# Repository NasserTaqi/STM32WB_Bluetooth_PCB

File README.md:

# STM32WB Bluetooth PCB
This project is a PCB built around an STM32WB for RF Bluetooth connection.

## Components
- STM32WB
- Crystal Oscillators:
    - HSE 32MHz 
    - LSE 32.768KHz
- 3.3V LDO
- USB C 2.0 + ESD protection
- Bluetooth RF connection via UFL connector + Filtering
- SWD Tag connect
- UART Connection

## Board Setup
The board is 4 layers with the following stack-up:

Layer: 1	SIGNAL

Layer: 2	GND

Layer: 3	GND

Layer: 4	SIGNAL

### Schematic:

### PCB Layout:

### PCB 3D:

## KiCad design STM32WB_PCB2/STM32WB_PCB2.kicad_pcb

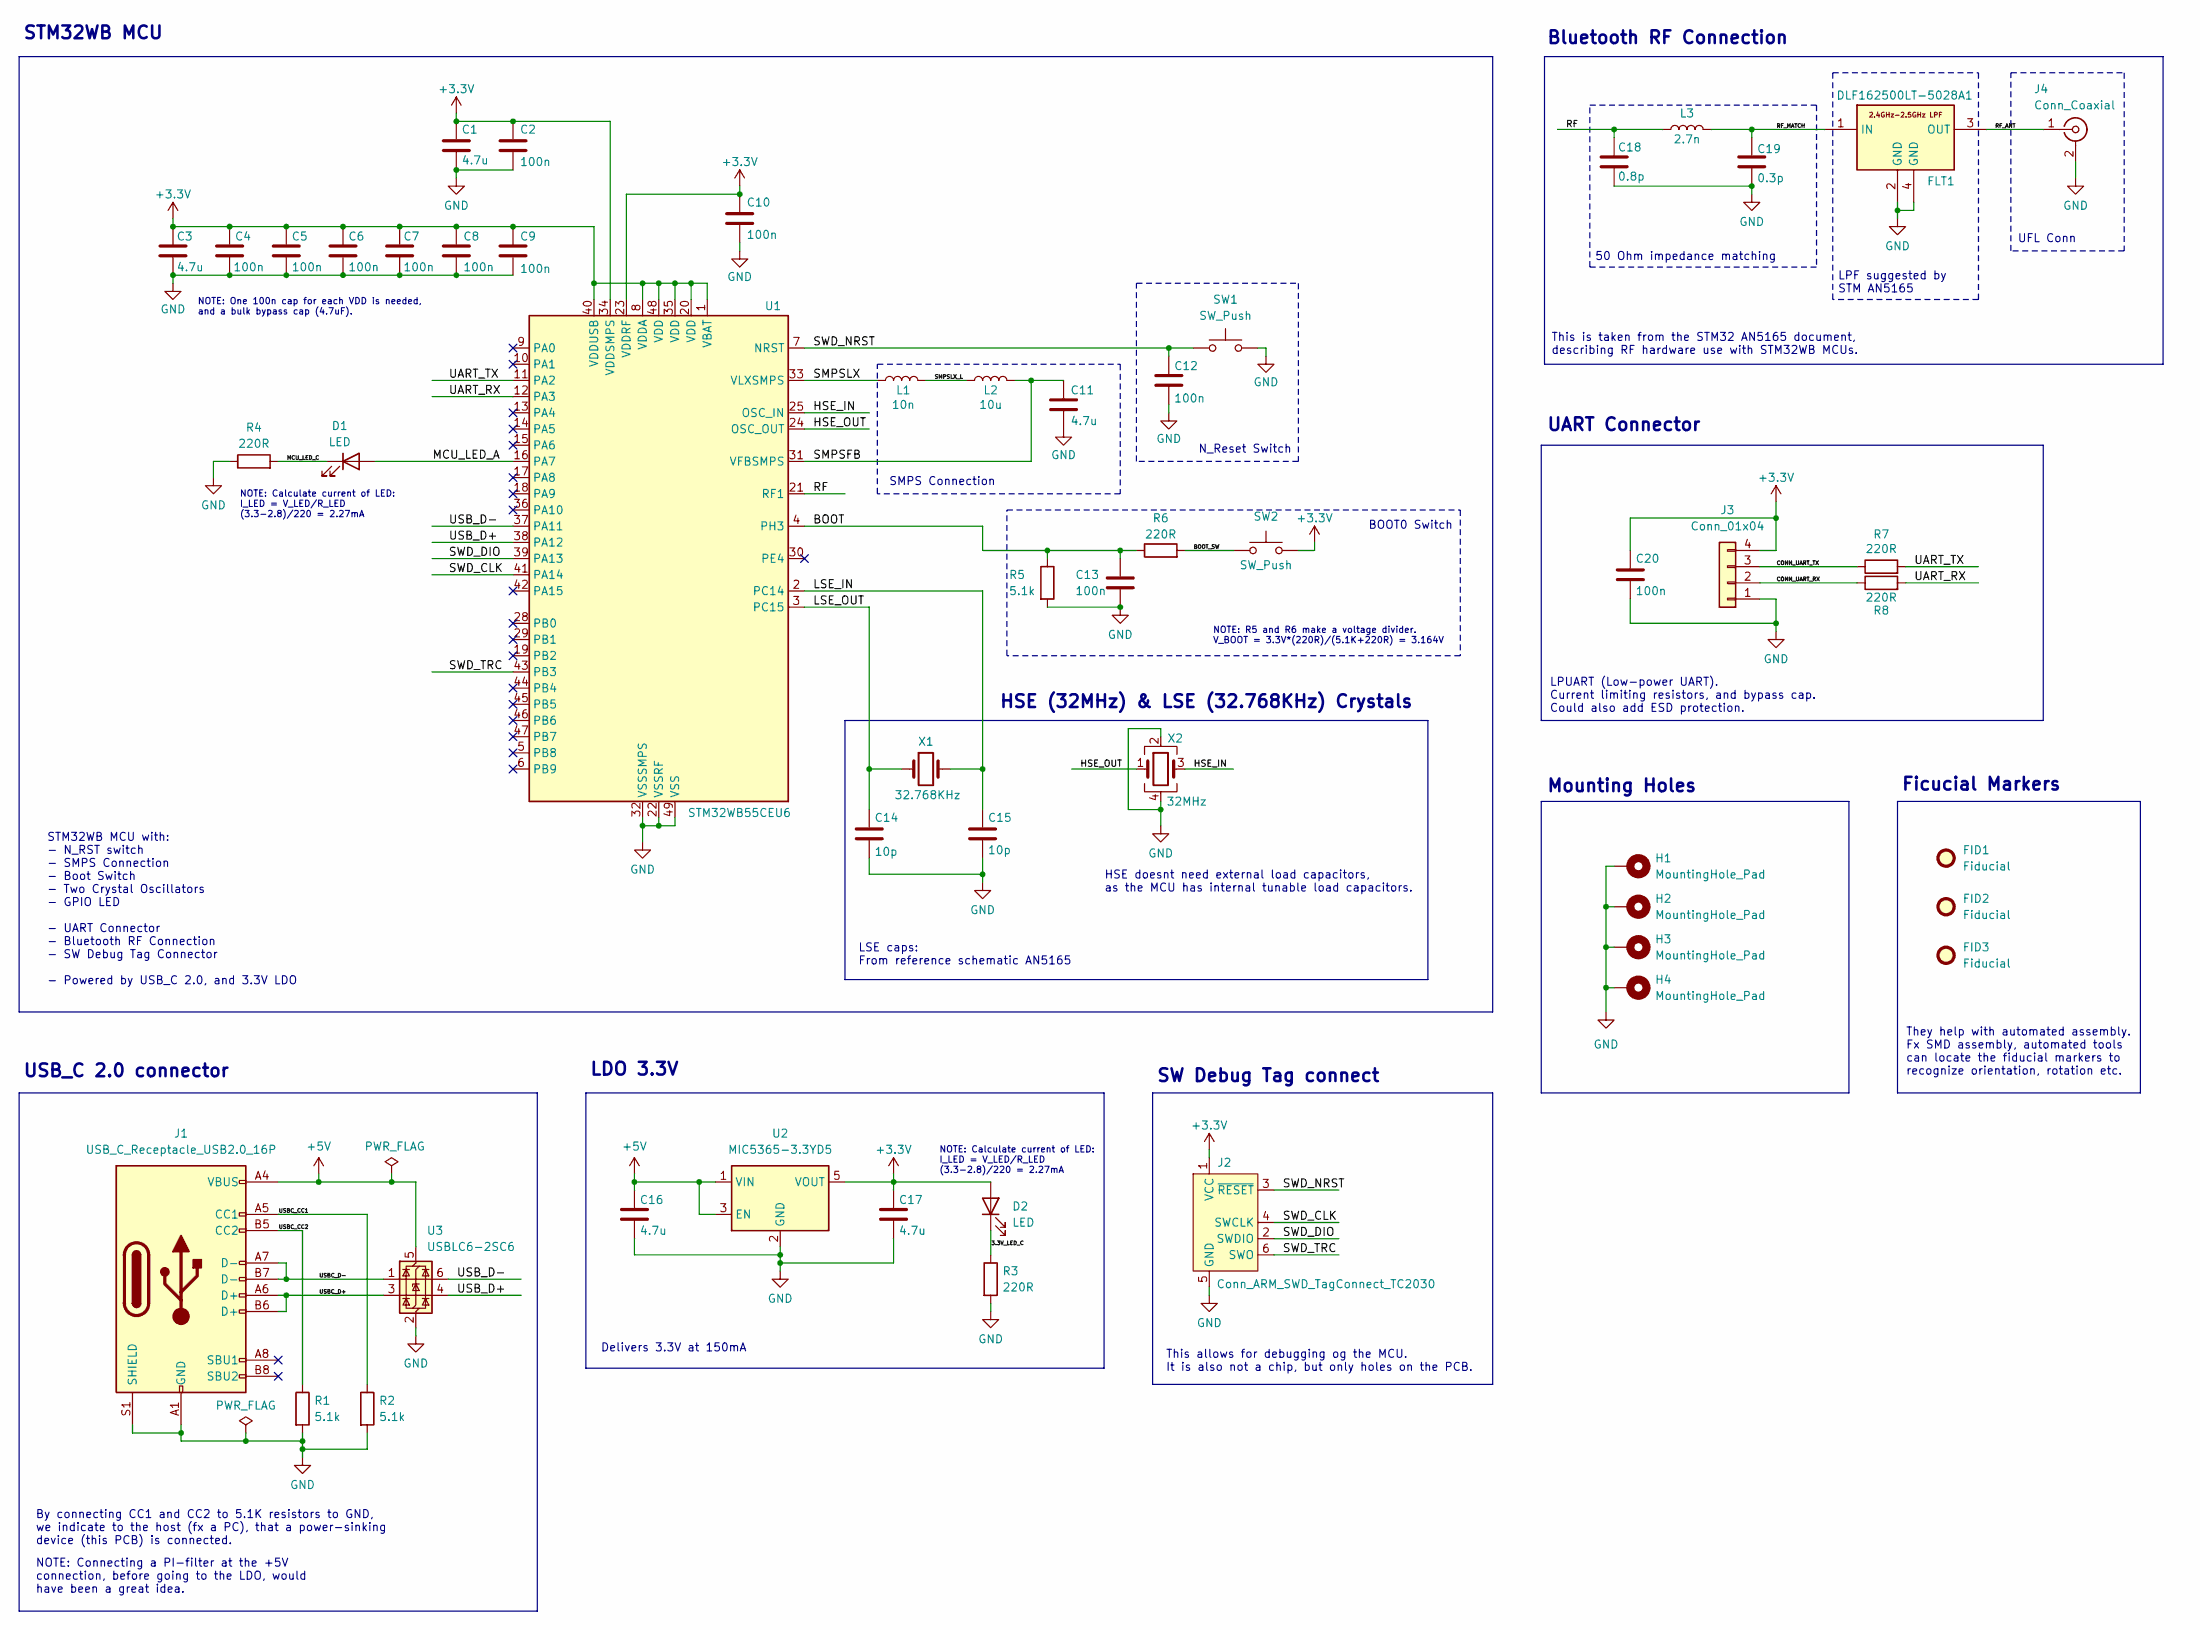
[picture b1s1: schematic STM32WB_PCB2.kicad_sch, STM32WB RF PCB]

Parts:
C1, C3, C11, C16, C17: 4.7u; C_0603_1608Metric; Manufacturer Part Number 0402ZD475KAT2A
C2, C4, C5, C6, C7, C8, C9, C10, C12, C13, C20: 100n; C_0402_1005Metric; Manufacturer Part Number C0402C104K4RAC3121
C14, C15: 10p; C_0402_1005Metric; Manufacturer Part Number C0402C100F8HACTU
C18: 0.8p; C_0402_1005Metric; Manufacturer Part Number GRM1555C1HR80BA01D
C19: 0.3p; C_0402_1005Metric; Manufacturer Part Number GRM1555C1HR30WA01D
D1, D2: LED; LED_0402_1005Metric; Manufacturer Part Number 599-1A90-147F
FID1, FID2, FID3: Fiducial; Fiducial_1mm_Mask2mm
FLT1: DLF162500LT-5028A1; DLF162500LT5028A1; Mouser Part Number 810-DLF16250LT5028A1
H1, H2, H3, H4: MountingHole_Pad; MountingHole_2.2mm_M2_Pad_Via
J1: USB_C_Receptacle_USB2.0_16P; USB_C_Receptacle_GCT_USB4105-xx-A_16P_TopMnt_Horizontal; Manufacturer Part Number USB4105-GF-A
J2: Conn_ARM_SWD_TagConnect_TC2030; Tag-Connect_TC2030-IDC-FP_2x03_P1.27mm_Vertical
J3: Conn_01x04; PinHeader_1x04_P2.54mm_Vertical; Manufacturer Part Number 22-28-4044
J4: Conn_Coaxial; U.FL_Hirose_U.FL-R-SMT-1_Vertical; Manufacturer Part Number U.FL-R-SMT(01)
L1: 10n; L_0402_1005Metric; Manufacturer Part Number LQG15WH10NH02D
L2: 10u; L_0805_2012Metric; Manufacturer Part Number LQM21DH100M70L
L3: 2.7n; L_0402_1005Metric; Manufacturer Part Number LQG15HN2N7C02D
R1, R2, R5: 5.1k; R_0402_1005Metric; Manufacturer Part Number RP0402BRD075K1L
R3, R4, R6, R7, R8: 220R; R_0402_1005Metric; Manufacturer Part Number RT0402BRD07220RL
SW1, SW2: SW_Push; SW_Push_SPST_NO_Alps_SKRK; Manufacturer Part Number SKRKAHE020
U1: STM32WB55CEU6; QFN-48-1EP_7x7mm_P0.5mm_EP5.6x5.6mm; Manufacturer Part Number STM32WB55CEU6
U2: MIC5365-3.3YD5; TSOT-23-5; Manufacturer Part Number MIC5365-3.3YD5-TR
U3: USBLC6-2SC6; SOT-23-6; Manufacturer Part Number USBLC6-2SC6
X1: 32.768KHz; Crystal_SMD_2012-2Pin_2.0x1.2mm; Manufacturer Part Number NX2012SA-32.768K-STD-MUB-1
X2: 32MHz; Crystal_SMD_2016-4Pin_2.0x1.6mm; Manufacturer Part Number NX2016SA-32M-EXS00A-CS06465

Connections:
+3.3V: C1.1, C2.1, C3.1, C4.1, C5.1, C6.1, C7.1, C8.1, C9.1, C10.1, C17.1, C20.1, D2.2 (A), J2.1 (VCC), J3.4, SW2.2, U1.1 (VBAT), U1.8 (VDDA), U1.20 (VDD), U1.23 (VDDRF), U1.34 (VDDSMPS), U1.35 (VDD), U1.40 (VDDUSB), U1.48 (VDD), U2.5 (VOUT)
+5V: C16.1, J1.A4 (VBUS), J1.A9 (VBUS), J1.B4 (VBUS), J1.B9 (VBUS), U2.1 (VIN), U2.3 (EN), U3.5 (VBUS)
/3.3V_LED_C: D2.1 (K), R3.1
/BOOT: C13.1, R5.1, R6.1, U1.4 (PH3)
/BOOT_SW: R6.2, SW2.1
/CONN_UART_RX: J3.2, R8.1
/CONN_UART_TX: J3.3, R7.1
/HSE_IN: U1.25 (OSC_IN), X2.3
/HSE_OUT: U1.24 (OSC_OUT), X2.1
/LSE_IN: C15.1, U1.2 (PC14), X1.2
/LSE_OUT: C14.1, U1.3 (PC15), X1.1
/MCU_LED_A: D1.2 (A), U1.16 (PA7)
/MCU_LED_C: D1.1 (K), R4.2
/RF: C18.1, L3.1, U1.21 (RF1)
/RF_ANT: FLT1.3 (OUT), J4.1 (In)
/RF_MATCH: C19.1, FLT1.1 (IN), L3.2
/SMPSFB: C11.1, L2.2, U1.31 (VFBSMPS)
/SMPSLX: L1.1, U1.33 (VLXSMPS)
/SMPSLX_L: L1.2, L2.1
/SWD_CLK: J2.4 (SWCLK), U1.41 (PA14)
/SWD_DIO: J2.2 (SWDIO), U1.39 (PA13)
/SWD_NRST: C12.1, J2.3 (~RESET), SW1.1, U1.7 (NRST)
/SWD_TRC: J2.6 (SWO), U1.43 (PB3)
/UART_RX: R8.2, U1.12 (PA3)
/UART_TX: R7.2, U1.11 (PA2)
/USBC_CC1: J1.A5 (CC1), R2.1
/USBC_CC2: J1.B5 (CC2), R1.1
/USBC_D+: J1.A6 (D+), J1.B6 (D+), U3.3 (I/O2)
/USBC_D-: J1.A7 (D-), J1.B7 (D-), U3.1 (I/O1)
/USB_D+: U1.38 (PA12), U3.4 (I/O2)
/USB_D-: U1.37 (PA11), U3.6 (I/O1)
GND: C1.2, C2.2, C3.2, C4.2, C5.2, C6.2, C7.2, C8.2, C9.2, C10.2, C11.2, C12.2, C13.2, C14.2, C15.2, C16.2, C17.2, C18.2, C19.2, C20.2, FLT1.2 (GND), FLT1.4 (GND), H1.1, H2.1, H3.1, H4.1, J1.A1 (GND), J1.A12 (GND), J1.B1 (GND), J1.B12 (GND), J1.S1 (SHIELD), J2.5 (GND), J3.1, J4.2 (Ext), R1.2, R2.2, R3.2, R4.1, R5.2, SW1.2, U1.22 (VSSRF), U1.32 (VSSSMPS), U1.49 (VSS), U2.2 (GND), U3.2 (GND), X2.2, X2.4

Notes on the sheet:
UFL Conn
STM32WB MCU with: - N_RST switch - SMPS Connection - Boot Switch - Two Crystal Oscillators - GPIO LED - UART Connector - Bluetooth RF Connection - SW Debug Tag Connector - Powered by USB_C 2.0, and 3.3V LDO
NOTE: R5 and R6 make a voltage divider. V_BOOT = 3.3V*(220R)/(5.1K+220R) = 3.164V
Mounting Holes
NOTE: One 100n cap for each VDD is needed, and a bulk bypass cap (4.7uF).
BOOT0 Switch
UART Connector
Ficucial Markers
HSE (32MHz) & LSE (32.768KHz) Crystals
LSE caps: From reference schematic AN5165
SW Debug Tag connect
LDO 3.3V
By connecting CC1 and CC2 to 5.1K resistors to GND, we indicate to the host (fx a PC), that a power-sinking device (this PCB) is connected.
They help with automated assembly. Fx SMD assembly, automated tools can locate the fiducial markers to recognize orientation, rotation etc.
LPUART (Low-power UART). Current limiting resistors, and bypass cap. Could also add ESD protection.
Delivers 3.3V at 150mA
This allows for debugging og the MCU. It is also not a chip, but only holes on the PCB.
SMPS Connection
This is taken from the STM32 AN5165 document, describing RF hardware use with STM32WB MCUs.
NOTE: Calculate current of LED: I_LED = V_LED/R_LED (3.3-2.8)/220 = 2.27mA
N_Reset Switch
Bluetooth RF Connection
50 Ohm impedance matching
HSE doesnt need external load capacitors, as the MCU has internal tunable load capacitors.
STM32WB MCU
USB_C 2.0 connector
NOTE: Connecting a PI-filter at the +5V connection, before going to the LDO, would have been a great idea.
LPF suggested by STM AN5165

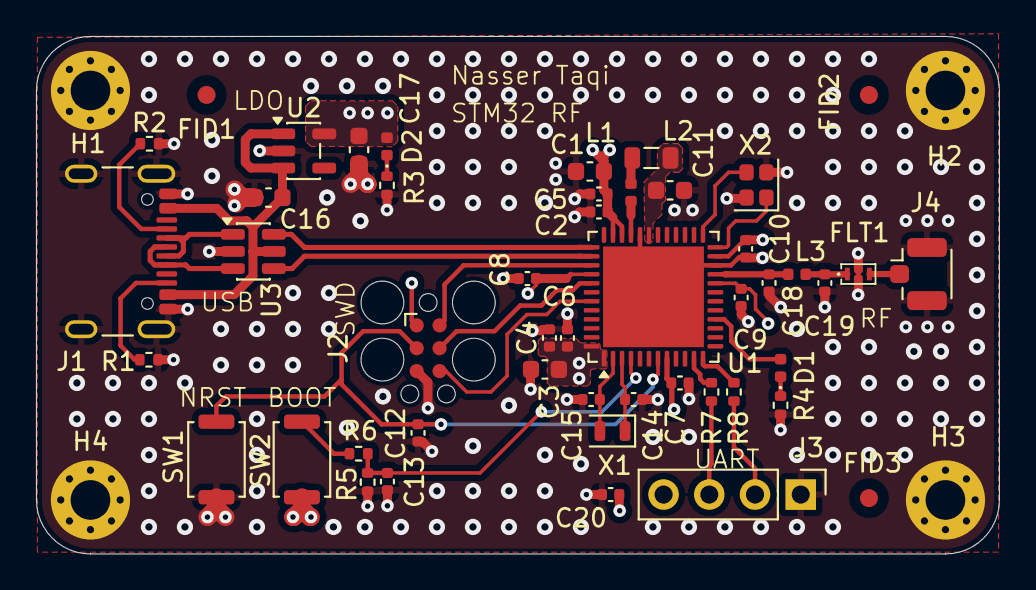
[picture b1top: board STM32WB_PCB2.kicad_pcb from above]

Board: 4 copper layers, 53.5 x 28.8 mm, 52 parts (0 on the bottom side), 32 nets.

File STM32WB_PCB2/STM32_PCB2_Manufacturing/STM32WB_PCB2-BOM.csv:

"Reference","Value","Footprint","Description","Manufacturer","Manufacturer Part Number","Distributor Link","Qty"
"C1,C3,C11,C16,C17","4.7u","Capacitor_SMD:C_0603_1608Metric","Unpolarized capacitor","KYOCERA AVX","0402ZD475KAT2A","https://www.mouser.dk/ProductDetail/KYOCERA-AVX/0402ZD475KAT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","5"
"C2,C4,C5,C6,C7,C8,C9,C10,C12,C13,C20","100n","Capacitor_SMD:C_0402_1005Metric","Unpolarized capacitor","KEMET","C0402C104K4RAC3121","https://www.mouser.dk/ProductDetail/KEMET/C0402C104K4RAC3121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","11"
"C14,C15","10p","Capacitor_SMD:C_0402_1005Metric","Unpolarized capacitor","KEMET","C0402C100F8HACTU","https://www.mouser.dk/ProductDetail/KEMET/C0402C100F8HACTU?q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","2"
"C18","0.8p","Capacitor_SMD:C_0402_1005Metric","Unpolarized capacitor","Murata Electronics","GRM1555C1HR80BA01D","https://www.mouser.dk/ProductDetail/Murata-Electronics/GRM15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","1"
"C19","0.3p","Capacitor_SMD:C_0402_1005Metric","Unpolarized capacitor","Murata Electronics","GRM1555C1HR30WA01D","https://www.mouser.dk/ProductDetail/Murata-Electronics/GRM15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","1"
"D1,D2","LED","LED_SMD:LED_0402_1005Metric","Light emitting diode","Dialight","599-1A90-147F","https://www.mouser.dk/ProductDetail/Dialight/599-1A90-147F?q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","2"
"FID1,FID2,FID3","Fiducial","Fiducial:Fiducial_1mm_Mask2mm","Fiducial Marker","","","","3"
"FLT1","DLF162500LT-5028A1","Samacsys:DLF162500LT5028A1","Signal Conditioning LTCC LOW PASS FLTR 2400-2500MHz","TDK","DLF162500LT-5028A1","https://www.mouser.dk/ProductDetail/TDK/DLF162500LT-5028A1?q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","1"
"H1,H2,H3,H4","MountingHole_Pad","MountingHole:MountingHole_2.2mm_M2_Pad_Via","Mounting Hole with connection","","","","4"
"J1","USB_C_Receptacle_USB2.0_16P","Connector_USB:USB_C_Receptacle_GCT_USB4105-xx-A_16P_TopMnt_Horizontal","USB 2.0-only 16P Type-C Receptacle connector","GCT","USB4105-GF-A","https://www.mouser.dk/ProductDetail/GCT/USB4105-GF-A?qs=KUoI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","1"
"J2","Conn_ARM_SWD_TagConnect_TC2030","Connector:Tag-Connect_TC2030-IDC-FP_2x03_P1.27mm_Vertical","Tag-Connect ARM Cortex SWD JTAG connector, 6 pin","","","","1"
"J3","Conn_01x04","Connector_PinHeader_2.54mm:PinHeader_1x04_P2.54mm_Vertical","Generic connector, single row, 01x04, script generated (kicad-library-utils/schlib/autogen/connector/)","Molex","22-28-4044","https://www.mouser.dk/ProductDetail/Molex/22-28-4044?qs=Muwp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","1"
"J4","Conn_Coaxial","Connector_Coaxial:U.FL_Hirose_U.FL-R-SMT-1_Vertical","coaxial connector (BNC, SMA, SMB, SMC, Cinch/RCA, LEMO, ...)","Hirose Connector","U.FL-R-SMT(01)","https://www.mouser.dk/ProductDetail/Hirose-Connector/U.FL-R-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","1"
"L1","10n","Inductor_SMD:L_0402_1005Metric","Inductor","Murata Electronics","LQG15WH10NH02D","https://www.mouser.dk/ProductDetail/Murata-Electronics/LQG15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","1"
"L2","10u","Inductor_SMD:L_0805_2012Metric","Inductor","Murata Electronics","LQM21DH100M70L","https://www.mouser.dk/ProductDetail/Murata-Electronics/LQM21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","1"
"L3","2.7n","Inductor_SMD:L_0402_1005Metric","Inductor","Murata Electronics","LQG15HN2N7C02D","https://www.mouser.dk/ProductDetail/Murata-Electronics/LQG15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","1"
"R1,R2,R5","5.1k","Resistor_SMD:R_0402_1005Metric","Resistor","YAGEO","RP0402BRD075K1L","https://www.mouser.dk/ProductDetail/YAGEO/RP0402BRD075K1L?qs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","3"
"R3,R4,R6,R7,R8","220R","Resistor_SMD:R_0402_1005Metric","Resistor","YAGEO","RT0402BRD07220RL","https://www.mouser.dk/ProductDetail/YAGEO/RT0402BRD07220RL?q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","5"
"SW1,SW2","SW_Push","Button_Switch_SMD:SW_Push_SPST_NO_Alps_SKRK","Push button switch, generic, two pins","Alps Alpine","SKRKAHE020","https://www.mouser.dk/ProductDetail/Alps-Alpine/SKRKAHE020?q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","2"
"U1","STM32WB55CEU6","Package_DFN_QFN:QFN-48-1EP_7x7mm_P0.5mm_EP5.6x5.6mm","STMicroelectronics Arm Cortex-M4 MCU, 512KB flash, 256KB RAM, 64 MHz, 1.71-3.6V, 30 GPIO, UFQFPN48","STMicroelectronics","STM32WB55CEU6","https://www.mouser.dk/ProductDetail/STMicroelectronics/STM32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","1"
"U2","MIC5365-3.3YD5","Package_TO_SOT_SMD:TSOT-23-5","150mA Low-dropout Voltage Regulator, Vout 3.3V, Vin up to 5.5V, TSOT-23-5","Microchip Technology","MIC5365-3.3YD5-TR","https://www.mouser.dk/ProductDetail/Microchip-Technology/MIC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","1"
"U3","USBLC6-2SC6","Package_TO_SOT_SMD:SOT-23-6","Very low capacitance ESD protection diode, 2 data-line, SOT-23-6","STMicroelectronics","USBLC6-2SC6","https://www.mouser.dk/ProductDetail/STMicroelectronics/USBLC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","1"
"X1","32.768KHz","Crystal:Crystal_SMD_2012-2Pin_2.0x1.2mm","Two pin crystal","NDK","NX2012SA-32.768K-STD-MUB-1","https://www.mouser.dk/ProductDetail/NDK/NX2012SA-32.768K-STD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","1"
"X2","32MHz","Crystal:Crystal_SMD_2016-4Pin_2.0x1.6mm","Four pin crystal, GND on pins 2 and 4","NDK","NX2016SA-32M-EXS00A-CS06465","https://www.mouser.dk/ProductDetail/NDK/NX2016SA-32M-EXS00A-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","1"
